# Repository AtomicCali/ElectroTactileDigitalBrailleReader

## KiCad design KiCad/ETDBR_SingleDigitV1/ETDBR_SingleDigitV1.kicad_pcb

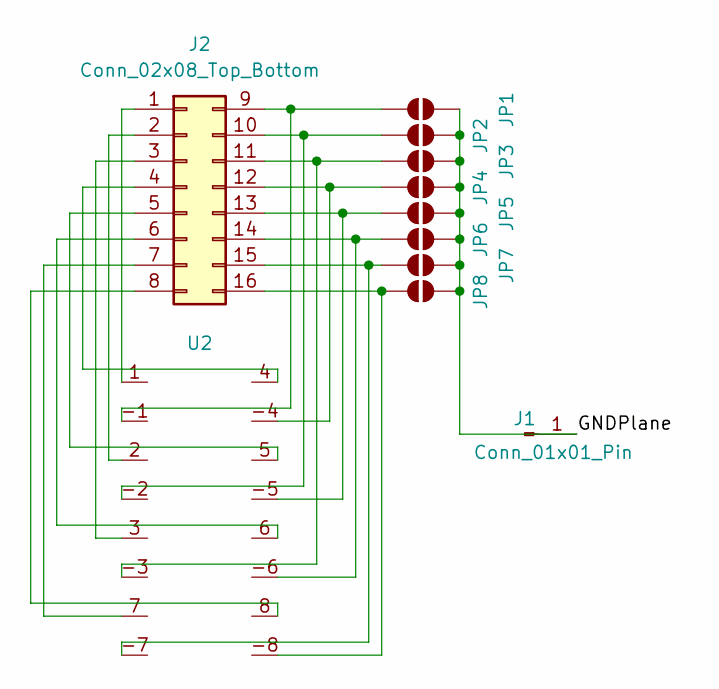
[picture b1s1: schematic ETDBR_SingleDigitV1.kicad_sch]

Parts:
J1: Conn_01x01_Pin; PinHeader_1x01_P2.54mm_Vertical
J2: Conn_02x08_Top_Bottom; IDC-Header_2x08_P2.54mm_Vertical
JP1, JP2, JP3, JP4, JP5, JP6, JP7, JP8: SolderJumper_2_Open; SolderJumper-2_P1.3mm_Open_TrianglePad1.0x1.5mm
U2: digitV1.1

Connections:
/GNDPlane: J1.1, JP1.2 (B), JP2.2 (B), JP3.2 (B), JP4.2 (B), JP5.2 (B), JP6.2 (B), JP7.2 (B), JP8.2 (B)
unnamed: J2.1, U2.1
unnamed: J2.2, U2.2
unnamed: J2.3, U2.3
unnamed: J2.4, U2.4
unnamed: J2.5, U2.5
unnamed: J2.6, U2.6
unnamed: J2.7, U2.7
unnamed: J2.8, U2.8
unnamed: J2.9, JP1.1 (A), U2.-1
unnamed: J2.10, JP2.1 (A), U2.-2
unnamed: J2.11, JP3.1 (A), U2.-3
unnamed: J2.12, JP4.1 (A), U2.-4
unnamed: J2.13, JP5.1 (A), U2.-5
unnamed: J2.14, JP6.1 (A), U2.-6
unnamed: J2.15, JP7.1 (A), U2.-7
unnamed: J2.16, JP8.1 (A), U2.-8

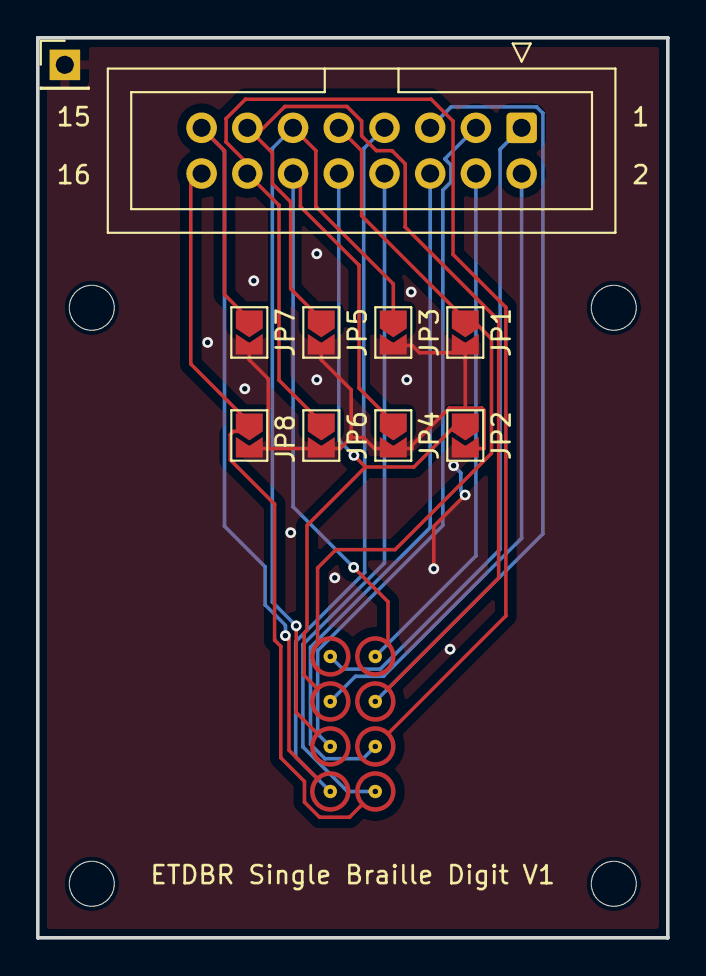
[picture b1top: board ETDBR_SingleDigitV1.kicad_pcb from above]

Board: 2 copper layers, 35.0 x 50.0 mm, 11 parts (0 on the bottom side), 17 nets.

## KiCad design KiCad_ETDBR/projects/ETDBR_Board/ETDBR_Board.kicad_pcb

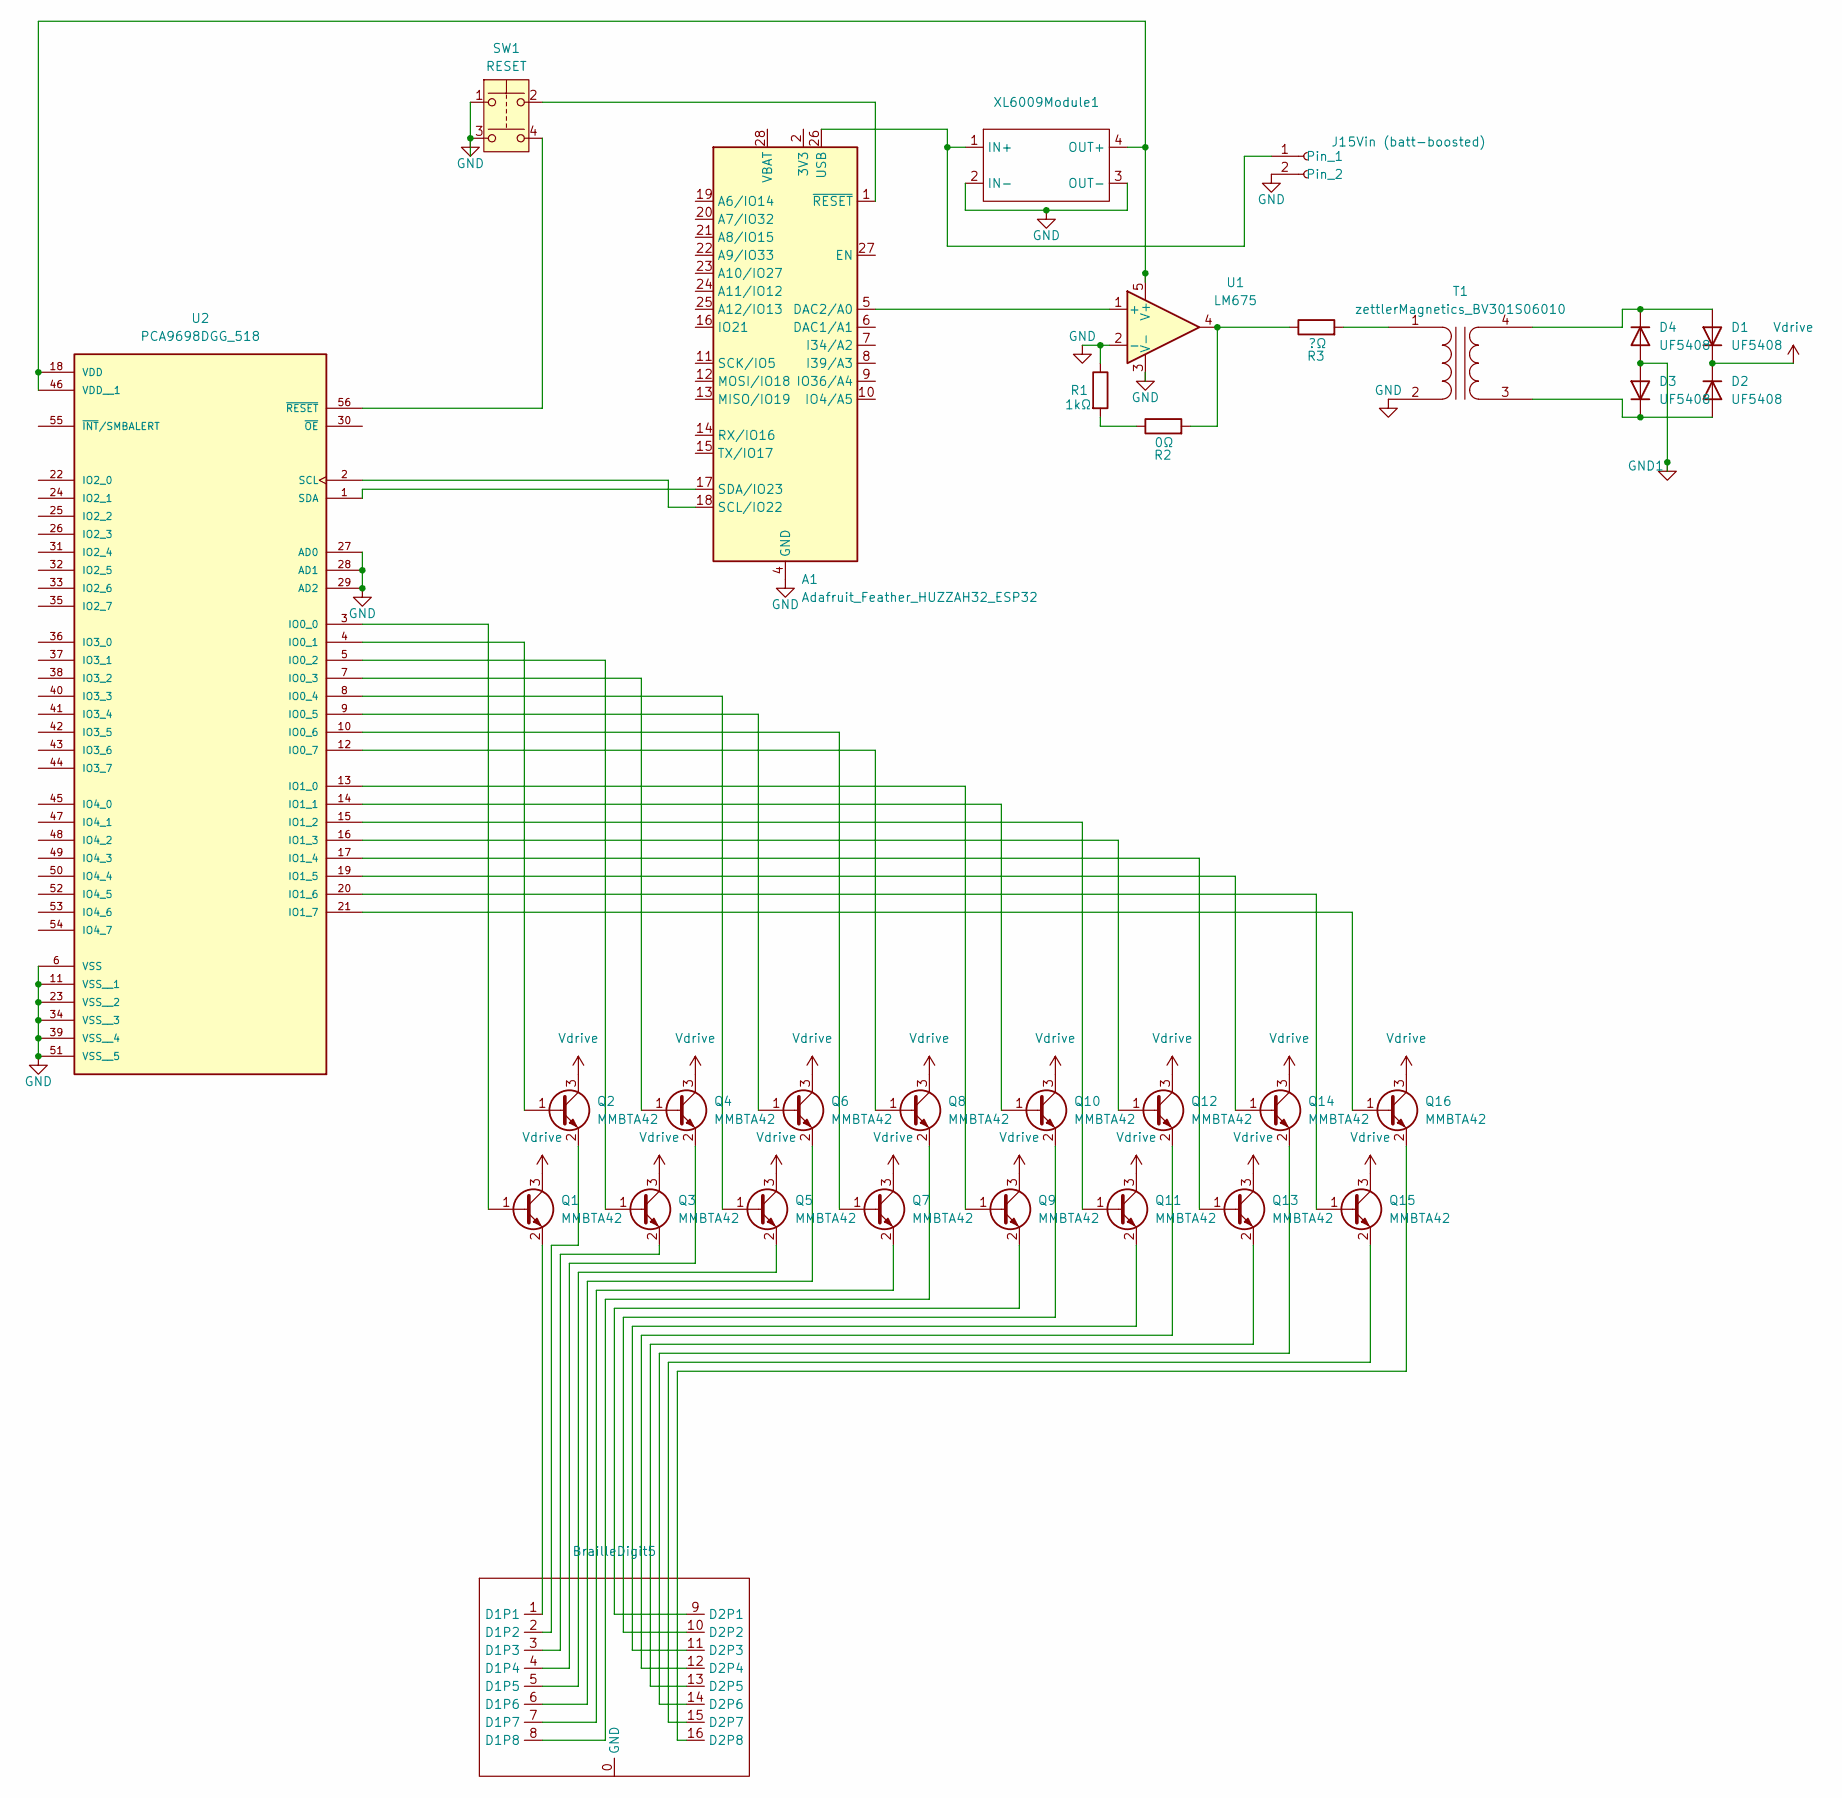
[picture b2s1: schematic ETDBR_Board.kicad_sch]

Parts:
A1: Adafruit_Feather_HUZZAH32_ESP32; Adafruit_Feather
BrailleDigit5: BraileDigit
D1, D2, D3, D4: UF5408; D_DO-201AD_P15.24mm_Horizontal
J1: 5Vin (batt-boosted); JST_PH_B2B-PH-K_1x02_P2.00mm_Vertical
Q1, Q2, Q3, Q4, Q5, Q6, Q7, Q8, Q9, Q10, Q11, Q12, Q13, Q14, Q15, Q16: MMBTA42; SOT-23-3
R1: 1kΩ; R_Axial_DIN0207_L6.3mm_D2.5mm_P7.62mm_Horizontal
R2: 0Ω; R_Axial_DIN0207_L6.3mm_D2.5mm_P7.62mm_Horizontal
R3: ?Ω; R_Axial_DIN0207_L6.3mm_D2.5mm_P7.62mm_Horizontal
SW1: RESET
T1: zettlerMagnetics_BV301S06010
U1: LM675; TO-220-5_P3.4x3.7mm_StaggerOdd_Lead3.8mm_Vertical
U2: PCA9698DGG_518; PCA9698-SOP50P810X120-56N; PARTREV 3
XL6009Module1: XL6009ModuleFOOT

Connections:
GND: A1.4 (GND), J1.2, R1.1, SW1.1, SW1.3, T1.2 (AB), U1.2 (-), U1.3 (V-), U2.6 (VSS), U2.11 (VSS__1), U2.23 (VSS__2), U2.27 (AD0), U2.28 (AD1), U2.29 (AD2), U2.34 (VSS__3), U2.39 (VSS__4), U2.51 (VSS__5), XL6009Module1.2 (IN-), XL6009Module1.3 (OUT-)
GND1: D3.2 (A), D4.2 (A)
unnamed: A1.5 (DAC2/A0), U1.1 (+)
unnamed: A1.18 (SCL/IO22), U2.2 (SCL)
unnamed: A1.17 (SDA/IO23), U2.1 (SDA)
unnamed: A1.26 (USB), J1.1, XL6009Module1.1 (IN+)
unnamed: A1.1 (~RESET), SW1.2
unnamed: BrailleDigit5.1 (D1P1), Q1.2 (E)
unnamed: BrailleDigit5.2 (D1P2), Q2.2 (E)
unnamed: BrailleDigit5.3 (D1P3), Q3.2 (E)
unnamed: BrailleDigit5.4 (D1P4), Q4.2 (E)
unnamed: BrailleDigit5.5 (D1P5), Q5.2 (E)
unnamed: BrailleDigit5.6 (D1P6), Q6.2 (E)
unnamed: BrailleDigit5.7 (D1P7), Q7.2 (E)
unnamed: BrailleDigit5.8 (D1P8), Q8.2 (E)
unnamed: BrailleDigit5.9 (D2P1), Q9.2 (E)
unnamed: BrailleDigit5.10 (D2P2), Q10.2 (E)
unnamed: BrailleDigit5.11 (D2P3), Q11.2 (E)
unnamed: BrailleDigit5.12 (D2P4), Q12.2 (E)
unnamed: BrailleDigit5.13 (D2P5), Q13.2 (E)
unnamed: BrailleDigit5.14 (D2P6), Q14.2 (E)
unnamed: BrailleDigit5.15 (D2P7), Q15.2 (E)
unnamed: BrailleDigit5.16 (D2P8), Q16.2 (E)
unnamed: D1.2 (A), D4.1 (K), T1.4 (SB)
unnamed: D2.2 (A), D3.1 (K), T1.3 (SA)
unnamed: Q1.1 (B), U2.3 (IO0_0)
unnamed: Q2.1 (B), U2.4 (IO0_1)
unnamed: Q3.1 (B), U2.5 (IO0_2)
unnamed: Q4.1 (B), U2.7 (IO0_3)
unnamed: Q5.1 (B), U2.8 (IO0_4)
unnamed: Q6.1 (B), U2.9 (IO0_5)
unnamed: Q7.1 (B), U2.10 (IO0_6)
unnamed: Q8.1 (B), U2.12 (IO0_7)
unnamed: Q9.1 (B), U2.13 (IO1_0)
unnamed: Q10.1 (B), U2.14 (IO1_1)
unnamed: Q11.1 (B), U2.15 (IO1_2)
unnamed: Q12.1 (B), U2.16 (IO1_3)
unnamed: Q13.1 (B), U2.17 (IO1_4)
unnamed: Q14.1 (B), U2.19 (IO1_5)
unnamed: Q15.1 (B), U2.20 (IO1_6)
unnamed: Q16.1 (B), U2.21 (IO1_7)
unnamed: R1.2, R2.1
unnamed: R2.2, R3.1, U1.4
unnamed: R3.2, T1.1 (AA)
unnamed: U1.5 (V+), U2.18 (VDD), U2.46 (VDD__1), XL6009Module1.4 (OUT+)
unnamed: SW1.4, U2.56 (~RESET)
Vdrive: D1.1 (K), D2.1 (K), Q1.3 (C), Q2.3 (C), Q3.3 (C), Q4.3 (C), Q5.3 (C), Q6.3 (C), Q7.3 (C), Q8.3 (C), Q9.3 (C), Q10.3 (C), Q11.3 (C), Q12.3 (C), Q13.3 (C), Q14.3 (C), Q15.3 (C), Q16.3 (C)

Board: 2 copper layers, 29 parts (11 on the bottom side), 44 nets, no tracks yet.

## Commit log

2024-10-28 init platfromio projects
2024-10-28 add kicad
2024-10-28 new ki cad project
2024-10-28 kicad autochanges
2024-10-28 added workspace file
2024-11-04 added thing in kicad
2024-12-04 kicad complete single digit design + gerber
2024-12-04 edits on single digit pcb in kicad with gerber
2024-12-06 file management
2024-12-12 pcb small text fix
